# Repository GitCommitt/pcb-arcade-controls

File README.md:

# README: pcb-arcade-controls

## Onderzoek

Bij het onderzoek zijn we begonnen met de PDF lezen en belangerijke dingen opslaan. We hebben aan het begin van dit process een [video](https://www.youtube.com/watch?v=8WXpGTIbxlQ) gekeken hoe we het software tool KiCad moeten gebruiken in combinatie met de STM32F072CBT6 Microprocessor.

## Kicad

In Kicad zijn we begonnen bij het maken van een nieuwe file met de template [library](https://github.com/GitCommitt/pcb-arcade-controls/tree/main/library/scottokeebs-main/Extras/ScottoModules/STM32F072CBT6) van de repo [Scottokeebs](https://github.com/joe-scotto/scottokeebs). Daarna hebben we voor het maken van een 3d model de [library](https://github.com/GitCommitt/pcb-arcade-controls/tree/main/library/scottokeebs-main/Extras/ScottoKicad/symbols) toegevoed aan onze preferences.

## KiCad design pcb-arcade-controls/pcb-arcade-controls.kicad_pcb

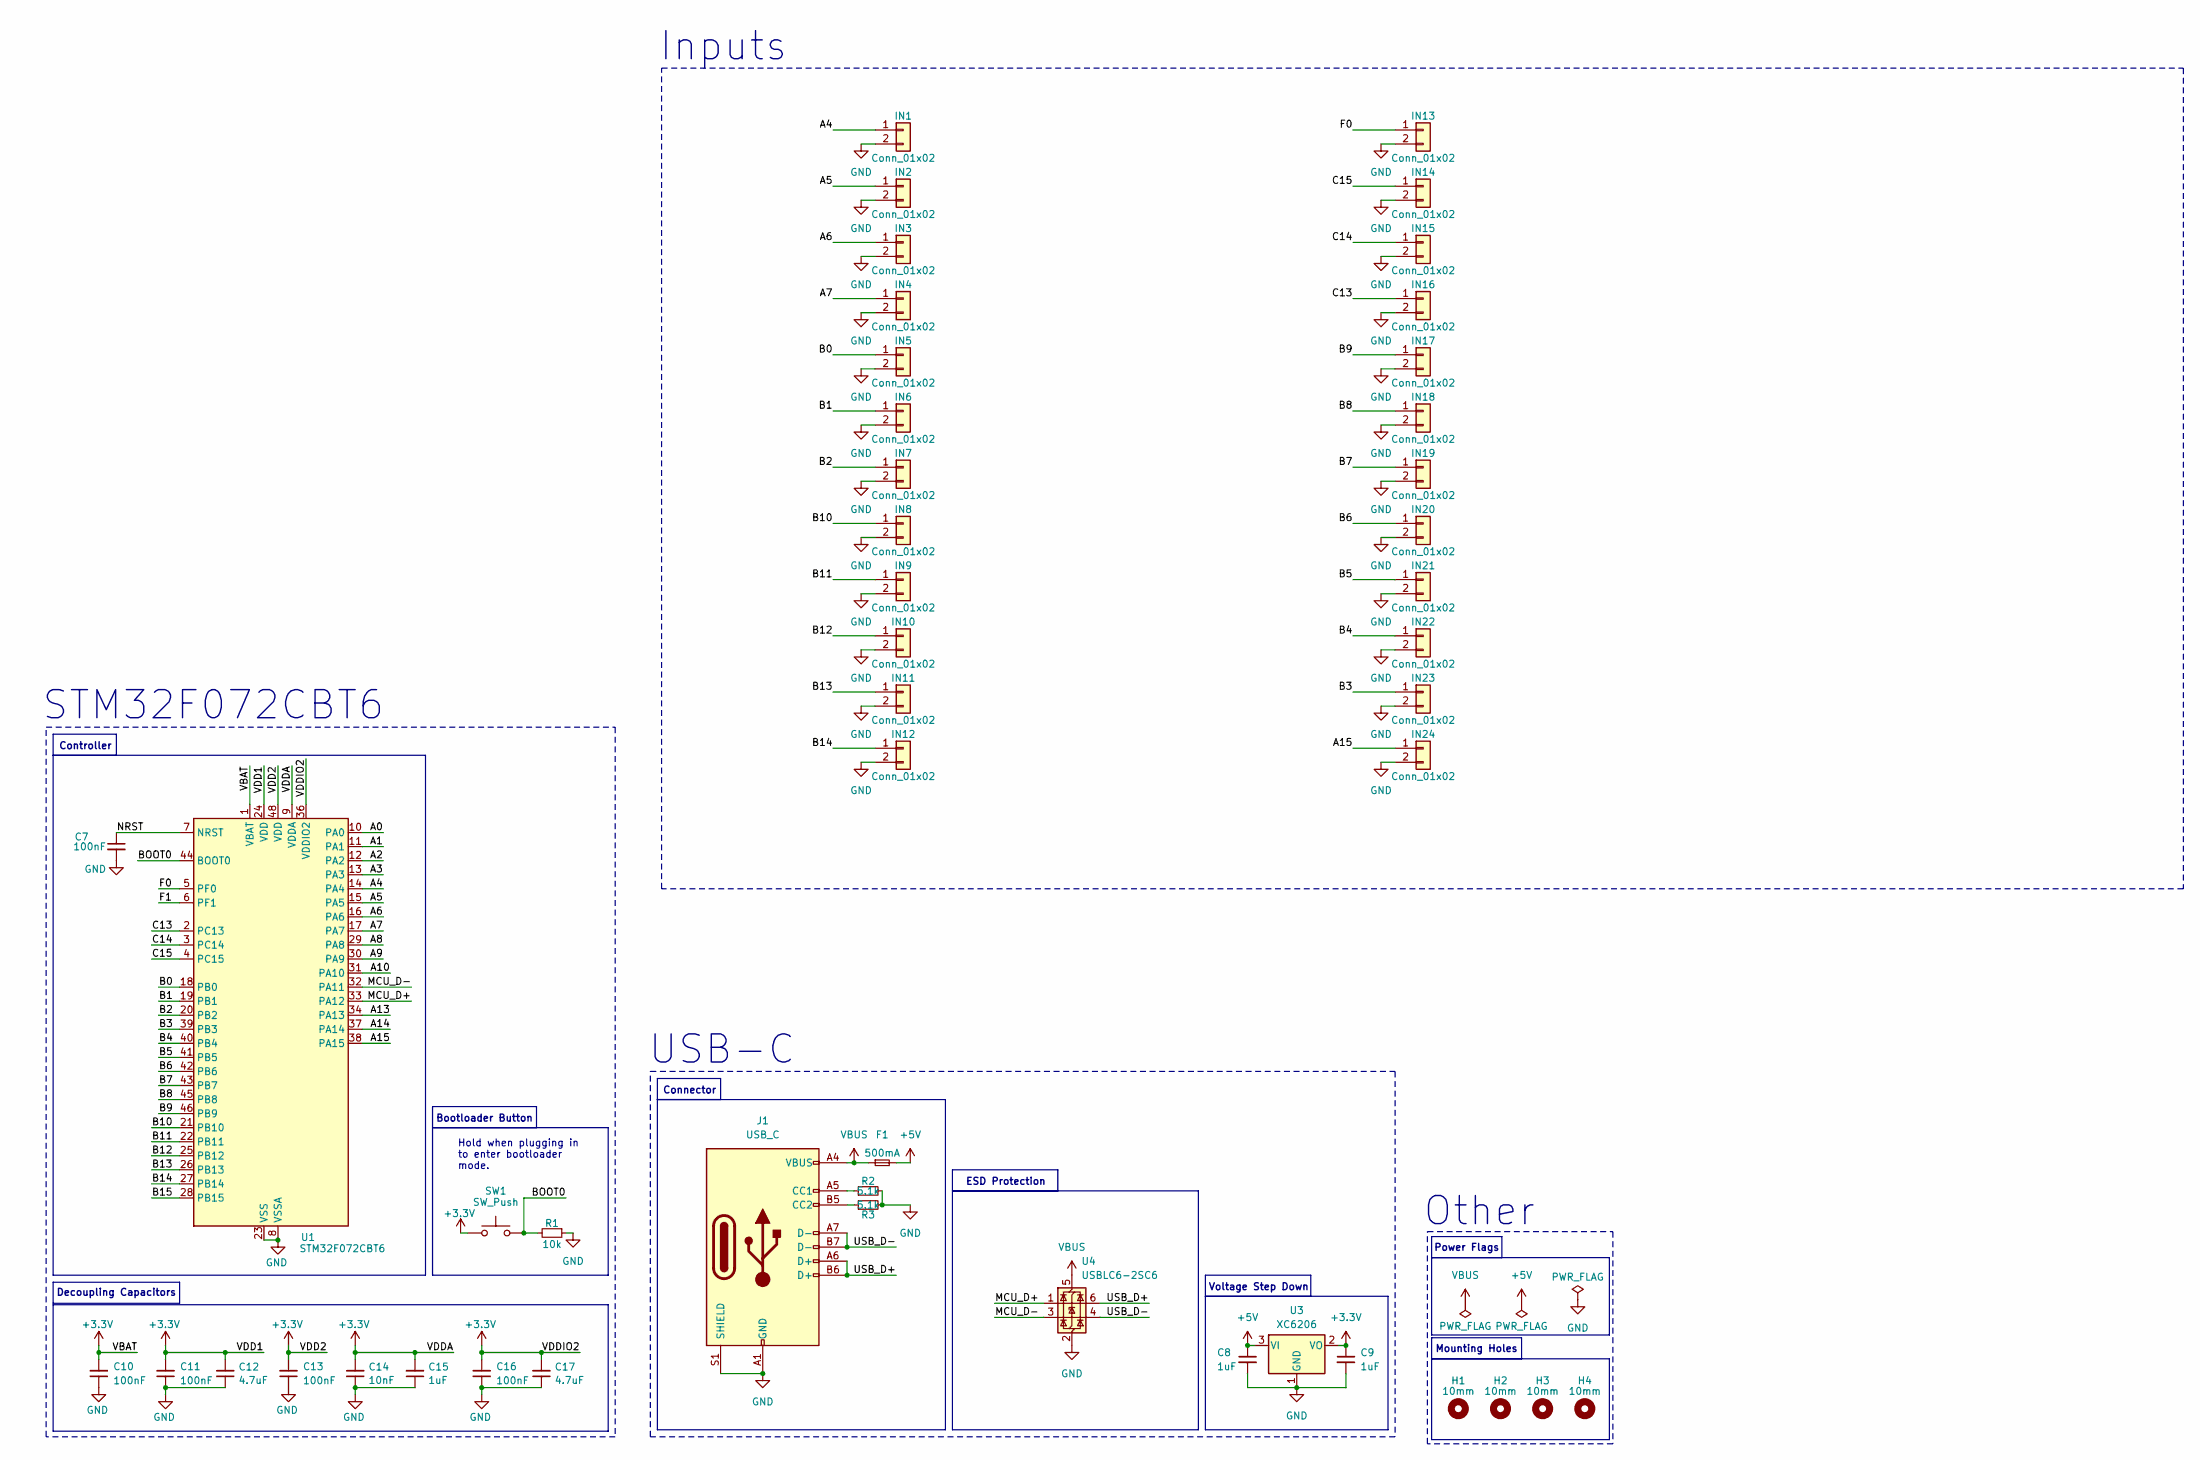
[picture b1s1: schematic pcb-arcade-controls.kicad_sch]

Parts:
C7: 100nF; Capacitor_0402; LCSC C307331
C8, C9: 1uF; Capacitor_0402; LCSC C52923
C10, C11, C13, C16: 100nF; Capacitor_0402; MPN CL05B104KB54PNC; LCSC C307331
C12, C17: 4.7uF; Capacitor_0402; MPN CL05A475MP5NRNC; LCSC C23733
C14: 10nF; Capacitor_0402; MPN CL05B103KB5NNNC; LCSC C15195
C15: 1uF; Capacitor_0402; MPN CL05A105KA5NQNC; LCSC C52923
F1: 500mA; Fuse_0603; LCSC C210357
H1, H2, H3, H4: 10mm; MountingHole_10mm
IN1, IN2, IN3, IN4, IN5, IN6, IN7, IN8, IN9, IN10, IN11, IN12, IN13, IN14, IN15, IN16, IN17, IN18, IN19, IN20, IN21, IN22, IN23, IN24: Conn_01x02; PinHeader_1x02_P2.54mm_Vertical
J1: USB_C; USB_C_HRO_TYPE-C-31-M-12; LCSC C165948
R1: 10k; Resistor_0402; LCSC C25744
R2, R3: 5.1k; Resistor_0402; LCSC C25905
SW1: SW_Push; Button_TL3342; LCSC C115351
U1: STM32F072CBT6; Package_LQFP-48_7x7mm_P0.5; LCSC C81720
U3: XC6206; Voltage_SOT-23; LCSC C5446
U4: USBLC6-2SC6; ESD_SOT-23-6; LCSC C2827654

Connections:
+3.3V: C9.1, C10.2, C11.2, C12.2, C13.2, C14.2, C15.2, C16.2, C17.2, SW1.1, U1.1 (VBAT), U1.9 (VDDA), U1.24 (VDD), U1.36 (VDDIO2), U1.48 (VDD), U3.2 (VO)
+5V: C8.1, F1.2, U3.3 (VI)
/A0: U1.10 (PA0)
/A1: U1.11 (PA1)
/A2: U1.12 (PA2)
/A3: U1.13 (PA3)
/A4: IN1.1, U1.14 (PA4)
/A5: IN2.1, U1.15 (PA5)
/A6: IN3.1, U1.16 (PA6)
/A7: IN4.1, U1.17 (PA7)
/A8: U1.29 (PA8)
/A9: U1.30 (PA9)
/A10: U1.31 (PA10)
/A13: U1.34 (PA13)
/A14: U1.37 (PA14)
/A15: IN24.1, U1.38 (PA15)
/B0: IN5.1, U1.18 (PB0)
/B1: IN6.1, U1.19 (PB1)
/B2: IN7.1, U1.20 (PB2)
/B3: IN23.1, U1.39 (PB3)
/B4: IN22.1, U1.40 (PB4)
/B5: IN21.1, U1.41 (PB5)
/B6: IN20.1, U1.42 (PB6)
/B7: IN19.1, U1.43 (PB7)
/B8: IN18.1, U1.45 (PB8)
/B9: IN17.1, U1.46 (PB9)
/B10: IN8.1, U1.21 (PB10)
/B11: IN9.1, U1.22 (PB11)
/B12: IN10.1, U1.25 (PB12)
/B13: IN11.1, U1.26 (PB13)
/B14: IN12.1, U1.27 (PB14)
/B15: U1.28 (PB15)
/BOOT0: R1.2, SW1.2, U1.44 (BOOT0)
/C13: IN16.1, U1.2 (PC13)
/C14: IN15.1, U1.3 (PC14)
/C15: IN14.1, U1.4 (PC15)
/F0: IN13.1, U1.5 (PF0)
/F1: U1.6 (PF1)
/MCU_D+: U1.33 (PA12), U4.1 (I/O1)
/MCU_D-: U1.32 (PA11), U4.3 (I/O2)
/NRST: C7.1, U1.7 (NRST)
/USB_D+: J1.A6 (D+), J1.B6 (D+), U4.6 (I/O1)
/USB_D-: J1.A7 (D-), J1.B7 (D-), U4.4 (I/O2)
GND: C7.2, C8.2, C9.2, C10.1, C11.1, C12.1, C13.1, C14.1, C15.1, C16.1, C17.1, IN1.2, IN2.2, IN3.2, IN4.2, IN5.2, IN6.2, IN7.2, IN8.2, IN9.2, IN10.2, IN11.2, IN12.2, IN13.2, IN14.2, IN15.2, IN16.2, IN17.2, IN18.2, IN19.2, IN20.2, IN21.2, IN22.2, IN23.2, IN24.2, J1.A1 (GND), J1.A12 (GND), J1.B1 (GND), J1.B12 (GND), J1.S1 (SHIELD), R1.1, R2.2, R3.2, U1.8 (VSSA), U1.23 (VSS), U1.35 (VSS), U1.47 (VSS), U3.1 (GND), U4.2 (GND)
unnamed: J1.A5 (CC1), R2.1
unnamed: J1.B5 (CC2), R3.1
VBUS: F1.1, J1.A4 (VBUS), J1.A9 (VBUS), J1.B4 (VBUS), J1.B9 (VBUS), U4.5 (VBUS)

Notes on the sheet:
STM32F072CBT6
USB-C
Mounting Holes
Decoupling Capacitors
Controller
ESD Protection
Power Flags
Voltage Step Down
Other
Bootloader Button
Inputs
Connector
Hold when plugging in to enter bootloader mode.

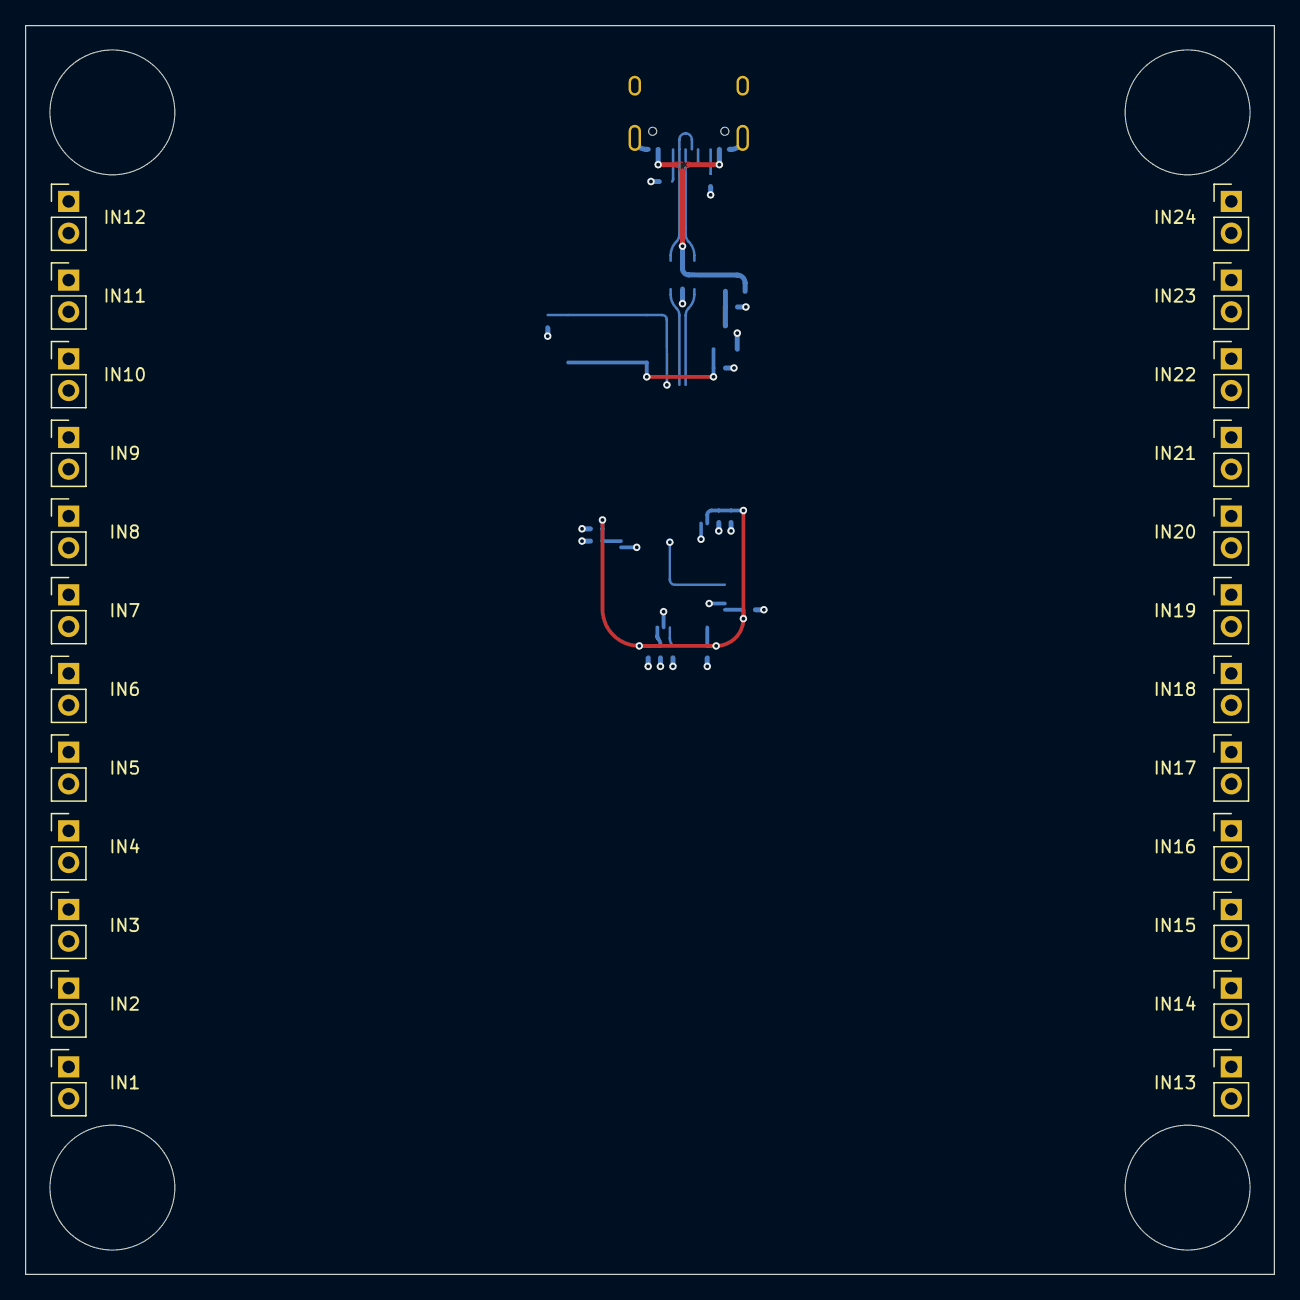
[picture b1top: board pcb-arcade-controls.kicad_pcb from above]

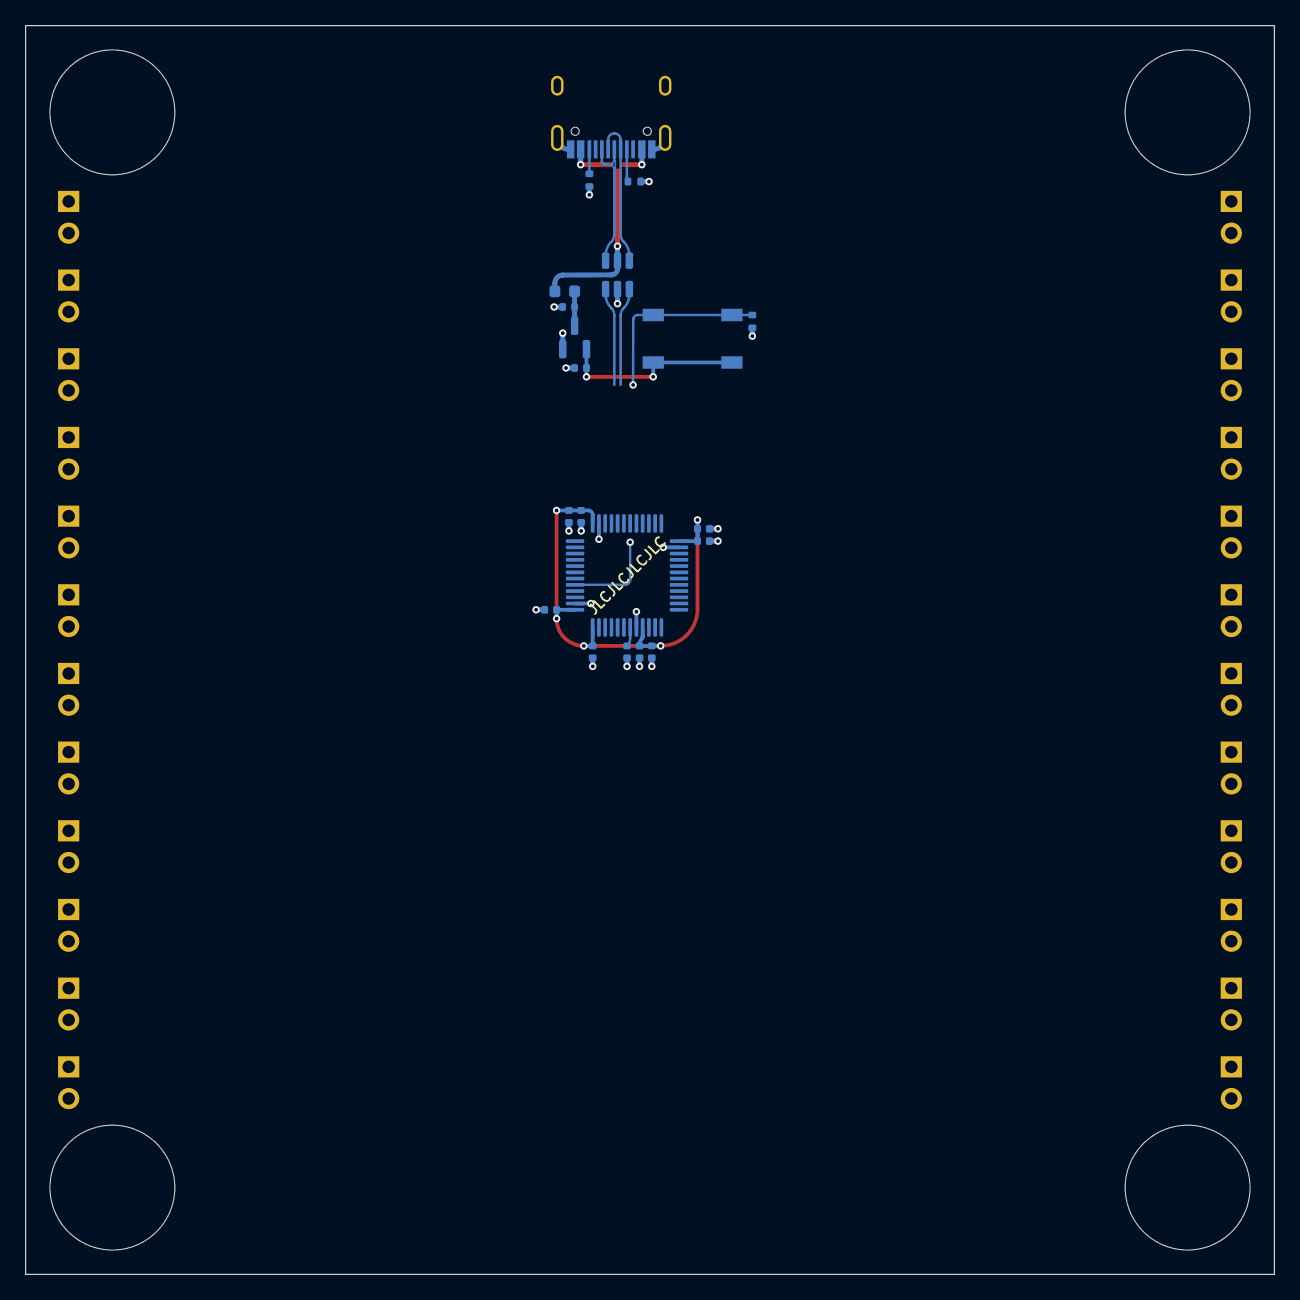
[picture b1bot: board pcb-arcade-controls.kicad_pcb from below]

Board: 4 copper layers, 100.0 x 100.0 mm, 48 parts (20 on the bottom side), 36 nets.
